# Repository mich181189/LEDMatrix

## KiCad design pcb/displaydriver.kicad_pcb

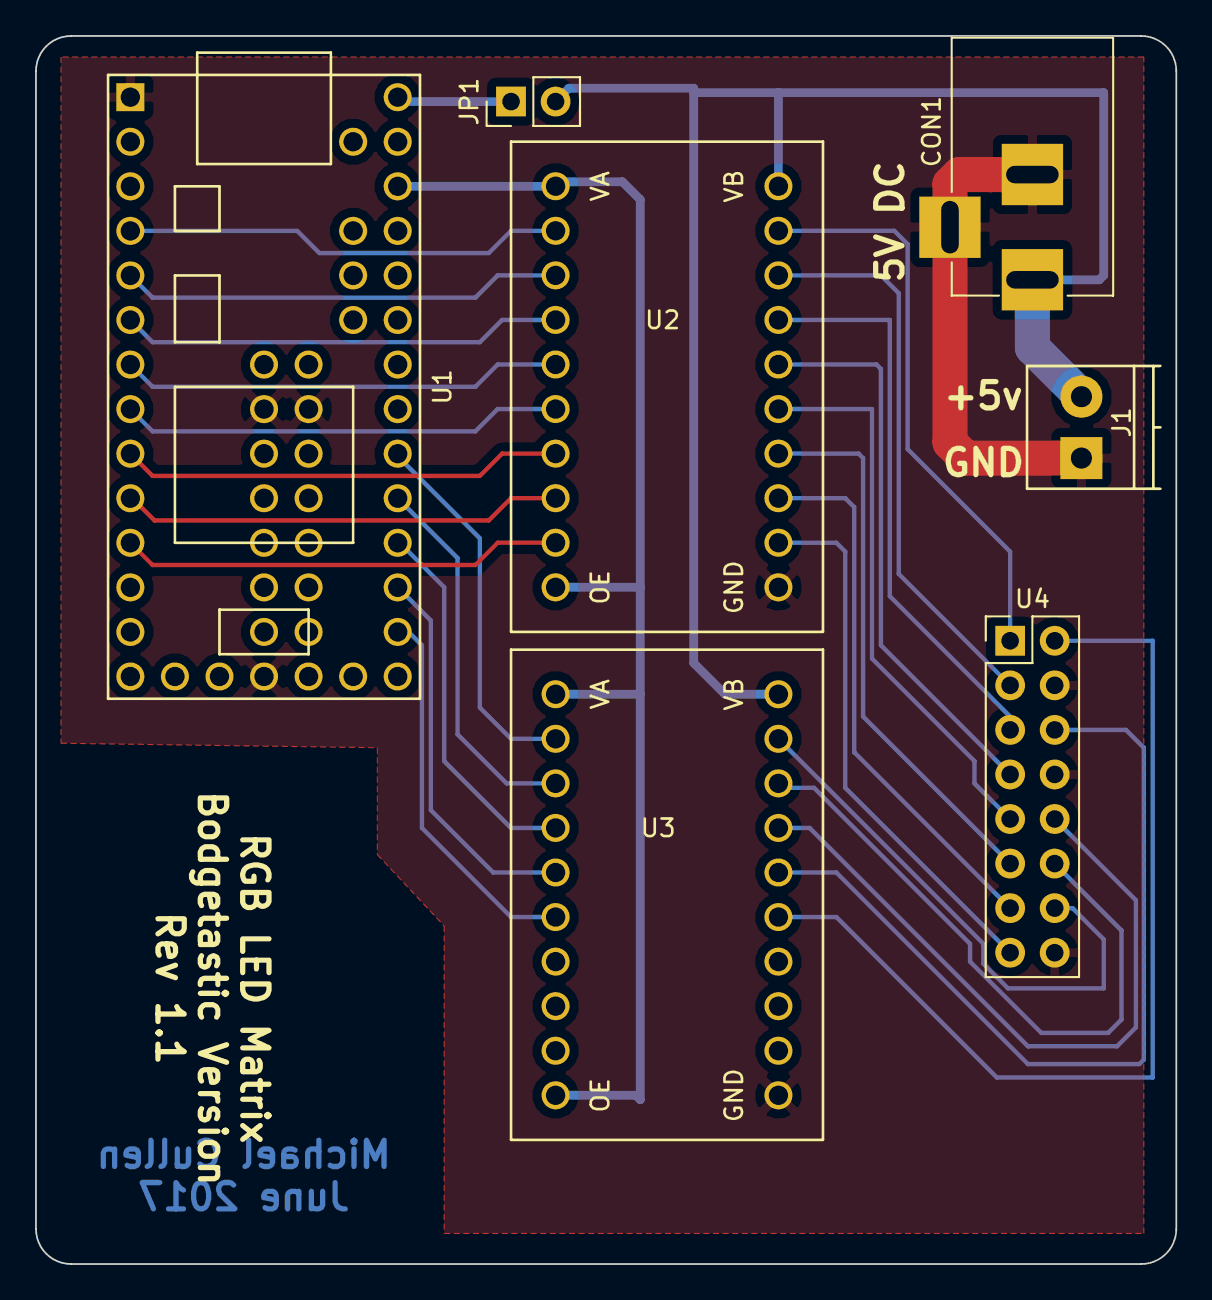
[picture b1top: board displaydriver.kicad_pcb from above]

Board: 2 copper layers, 65.0 x 70.0 mm, 7 parts (0 on the bottom side), 30 nets.

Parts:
CON1: BARREL_JACK
J1: Screw_Terminal_1x02; TerminalBlock_Pheonix_PT-3.5mm_2pol
JP1: Jumper_NO_Small; Pin_Header_Straight_1x02_Pitch2.54mm
U1: Teensy3.1; Teensy30_31_32_LC
U2, U3: TXB0108-PW; txb0108_breakout
U4: RGBLEDMTX; Pin_Header_Straight_2x08_Pitch2.54mm

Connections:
+3V3: U1.31, U2.2, U2.10, U3.2, U3.10
+5V: CON1.1, J1.2, JP1.2, U2.19, U3.19
GND: CON1.2, CON1.3, J1.1, U1.1, U1.17, U1.39, U1.50, U2.11, U3.11, U4.4, U4.8, U4.16
unnamed: JP1.1, U1.33
unnamed: U1.4, U2.1
unnamed: U1.5, U2.3
unnamed: U1.6, U2.4
unnamed: U1.7, U2.5
unnamed: U1.8, U2.6
unnamed: U1.9, U2.7
unnamed: U1.10, U2.8
unnamed: U1.11, U2.9
unnamed: U1.21, U3.6
unnamed: U1.22, U3.5
unnamed: U1.23, U3.4
unnamed: U1.24, U3.3
unnamed: U1.25, U3.1
unnamed: U2.12, U4.15
unnamed: U2.13, U4.13
unnamed: U2.14, U4.11
unnamed: U2.15, U4.9
unnamed: U2.16, U4.7
unnamed: U2.17, U4.5
unnamed: U2.18, U4.3
unnamed: U2.20, U4.1
unnamed: U3.15, U4.2
unnamed: U3.16, U4.6
unnamed: U3.17, U4.10
unnamed: U3.18, U4.12
unnamed: U3.20, U4.14

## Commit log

2017-01-08 Added first pass at PCB
2017-01-14 Rev 1.0 PCB
2017-01-18 Renamed christmas_display.ino to LEDMatrix.ino to fix arduino IDE problem
    Guess which IDE doesn't like the file name to be different to the folder?
2017-01-22 State as of US Election 2016 board
2017-01-22 Final changes for bodgetastic pcb v1.0
2017-02-08 Fixed a few PCB bugs and annoyances found on first run
2017-02-08 Swapped power plug out for barrel jack, left PCB partially unrouted since future changes are likely
2017-03-26 New patterns and timing logic
2017-06-02 WIP: Font
2017-06-02 PCB 1.1
2017-06-09 First pass of UK Election
2017-06-09 Avoid protocol screwup by sending LED counts to board to avoid overflowing
2017-06-09 Switched UKIP for SNP on the board
2017-06-09 Damn it CNN changed their feed's format slightly
2017-07-26 PCB: Fixed some silkscreen issues
2017-07-30 Bumped version on schematic to correct value
2017-07-30 Add letters to font
2017-07-30 added timing notes
